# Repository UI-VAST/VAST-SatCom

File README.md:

# VAST-SatCom

This repository contains the files for the raspberry pi used by the Vandals Atmospheric Science Team Satellite Communications System.

an Iridium python library used to send and receive data over the iridium network.

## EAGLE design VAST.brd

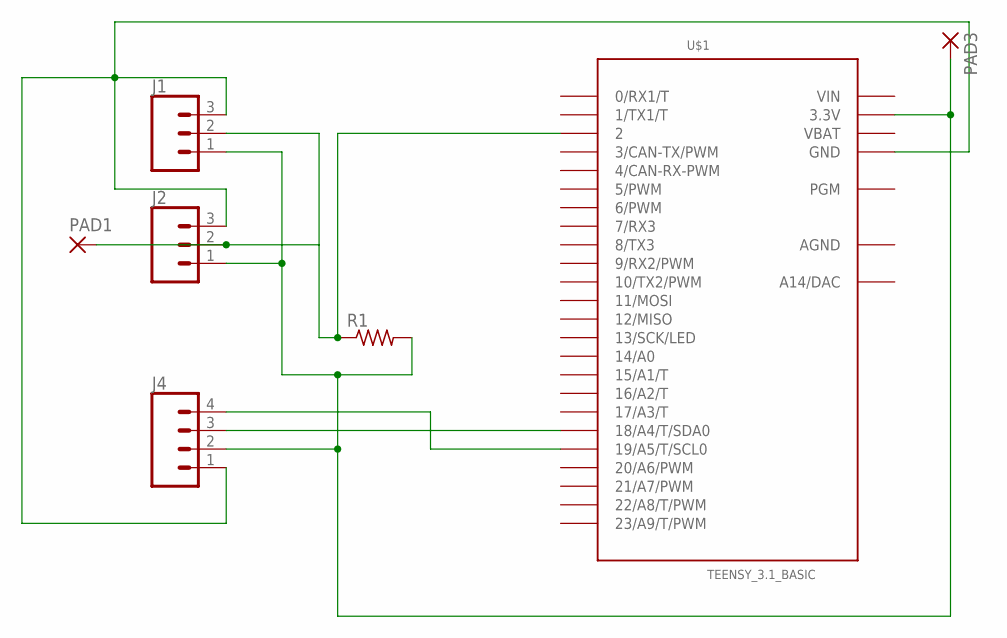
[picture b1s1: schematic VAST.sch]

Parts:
J1, J2: CONN_03POLAR_LOCK; MOLEX-1X3_LOCK
J4: CONN_04POLAR; MOLEX-1X4
PAD1, PAD3: SMD5; SMD2,54-5,08
R1: ADAFRUIT_R-US_0207/10; ADAFRUIT_0207/10
U$1: TEENSY_3.1_BASIC

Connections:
AGND: U$1.AGND
unnamed: J1.2, J2.2, PAD1.1, R1.1, U$1.2
unnamed: J1.1, J2.1, J4.2, PAD3.1, R1.2, U$1.3.3V, U$1.3.3V1 (3.3V)
unnamed: J4.3, U$1.18/A4 (18/A4/T/SDA0)
unnamed: J4.4, U$1.19/A5 (19/A5/T/SCL0)
unnamed: J1.3, J2.3, J4.1, U$1.GND, U$1.GND1 (GND)
VBAT: U$1.VBAT
VIN: U$1.VIN

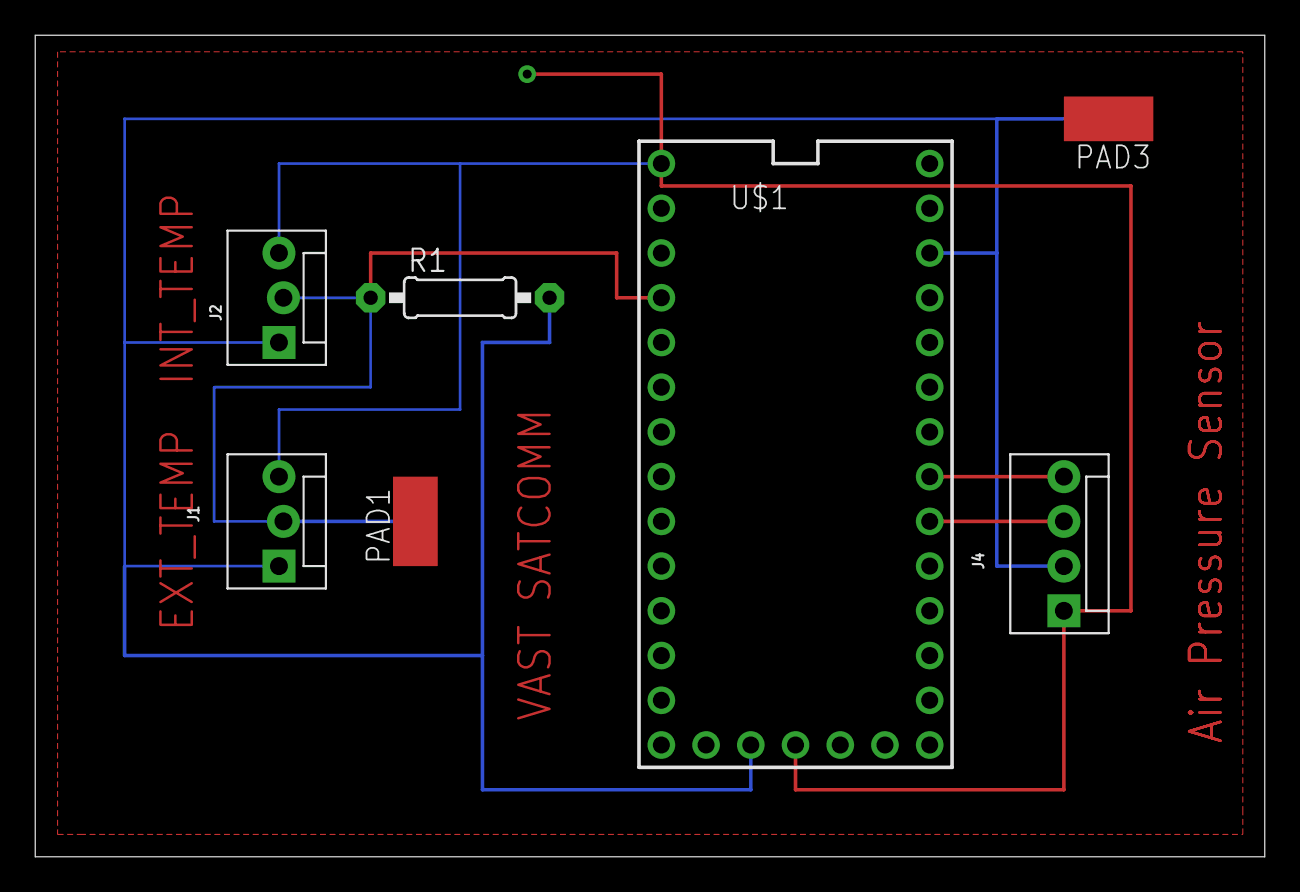
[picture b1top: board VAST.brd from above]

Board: 2 copper layers, 69.8 x 46.7 mm, 7 parts (0 on the bottom side), 5 nets.

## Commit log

2019-09-09 renaming
2019-09-09 Added dashboard directory
2019-09-11 added teensy .ino file for recording temperatures from sensors
2020-02-11 added brief todo in iridium python file
2020-02-27 Add files via upload
    Updated board with ground VIA and Two Test Pads
2020-03-11 added Iridium class. directories need reorganizing....
2020-03-11 updated AT command script.
2020-04-18 Added Iridium class/library under Payload directory.
2020-04-18 started iridium receiver program, for tracker vehicle
2020-04-19 logger
2020-04-19 rearrange transmitter
2020-04-19 rearranged iridium
2020-04-21 packet receiver now logs all received packets to file
2020-04-21 transmitter work

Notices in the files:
parts and their libraries:
SparkFun-Connectors: Licensing: Creative Commons ShareAlike 4.0 International - https://creativecommons.org/licenses/by-sa/4.0
